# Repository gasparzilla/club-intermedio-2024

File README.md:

# Club Nivelacion Mustakis
Este es el repositorio del club de robótica de nivelación para el primer semestre. Aquí encontrás todo lo necesario para ejecutar las sesiones de manera exitosa.

## Sesiones
- Las presentaciones PPT por sesión se pueden encontrar en el siguiente link: [Presentaciones](https://drive.google.com/drive/folders/1Q9-XKyEnKL0MnVXYtlh8kp2lwUHTAggA?usp=drive_link).
- Los tiempos sugeridos por sesión se pueden encontrar en el siguiente link: [Tiempos](https://docs.google.com/spreadsheets/d/1nqdYl0ClQ_0Gk07j1FVFSghQwln12yA571QY8IFsEMs/edit?usp=sharing)
- Videos útiles complementarios a las sesiones se pueden encontrar en el siguiente link: [Videos](https://docs.google.com/document/d/1KKutP_OMOU2o7BTJ72E6Tdv1sluavG1waSLBUKC-ohQ/edit?usp=sharing)
- La lista de materiales por sesión se puede encontrar en el siguiente link: [Materiales](https://docs.google.com/spreadsheets/d/13yleChsTLTt9z9LAu8KrCemjK9vvLF0Dbb_VBI3P-Ws/edit?usp=sharing)

## Solucionarios
Los solucionarios se encuentran dentro de este repositorio ordenados por sesión.

## Archivos de construcción
En caso de ser necesario, dentro de la carpeta KiCad, se encuentran los proyectos originales de los circuitos utilizados en el semestre. Estos contienen los esquemáticos y el diseño de la pcb. También se pueden encontrar los archivos 3D necesarios.

## Errores y sugerencias
En caso de que se encuentren errores de contenido y/o cualquier otro problema relacionado a las sesiones, por favor añadirlo como una Issue al repositorio, de esta manera se queda registro de los cambios realizados historicamente para futuras referencias en un único lugar.

---
*Trabajo realizado por Benjamin Espinoza y Gaspas Fábrega para el programa de Ciencia y Tecnología de la Fundación Mustakis, 2024*

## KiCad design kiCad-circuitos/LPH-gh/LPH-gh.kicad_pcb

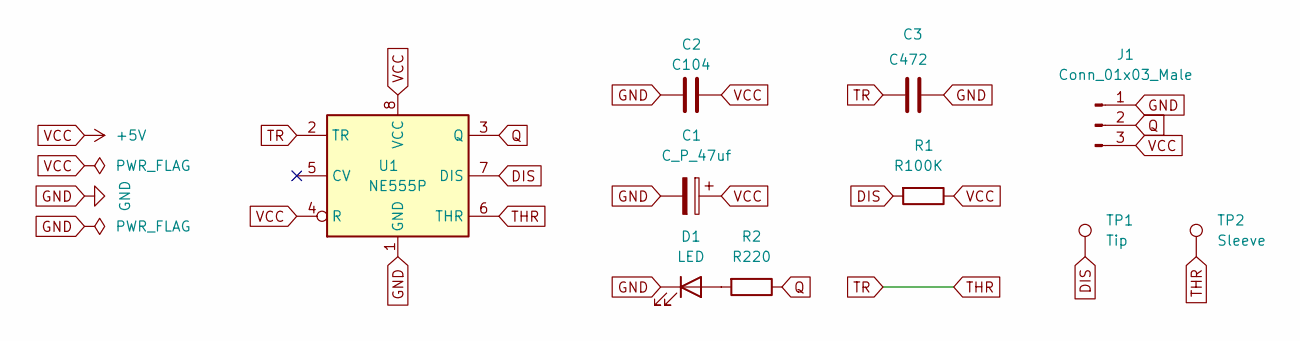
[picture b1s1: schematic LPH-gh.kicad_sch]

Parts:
C1: C_P_47uf; CP_Radial_D5.0mm_P2.00mm
C2: C104; C_Disc_D5.0mm_W2.5mm_P5.00mm
C3: C472; C_Disc_D5.0mm_W2.5mm_P5.00mm
D1: LED; LED_D5.0mm
J1: Conn_01x03_Male; PinHeader_1x03_P2.54mm_Vertical
R1: R100K; R_Axial_DIN0204_L3.6mm_D1.6mm_P7.62mm_Horizontal
R2: R220; R_Axial_DIN0204_L3.6mm_D1.6mm_P7.62mm_Horizontal
TP1: Tip; MountingHole_3mm_Pad
TP2: Sleeve; MountingHole_3mm_Pad
U1: NE555P; DIP-8_W7.62mm

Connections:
DIS: R1.2, TP1.1, U1.7 (DIS)
GND: C1.2, C2.2, C3.2, D1.1 (K), J1.1, U1.1 (GND)
unnamed: D1.2 (A), R2.2
Q: J1.2, R2.1, U1.3 (Q)
THR: C3.1, TP2.1, U1.2 (TR), U1.6 (THR)
VCC: C1.1, C2.1, J1.3, R1.1, U1.4 (R), U1.8 (VCC)

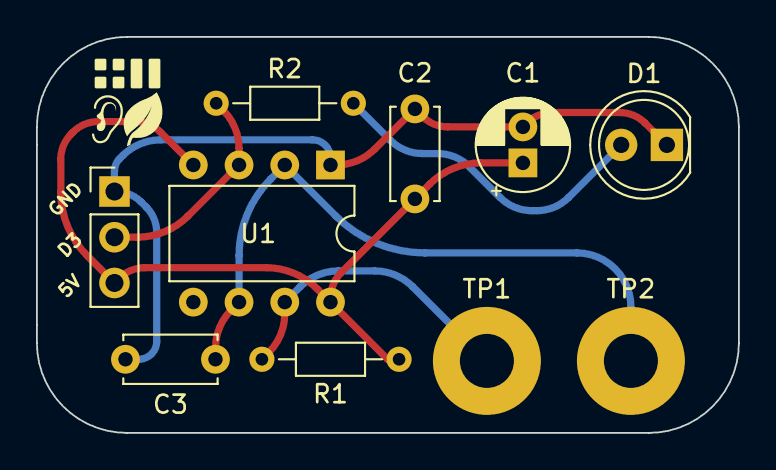
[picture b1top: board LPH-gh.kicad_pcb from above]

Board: 2 copper layers, 39.0 x 22.0 mm, 10 parts (0 on the bottom side), 6 nets.

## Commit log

2024-03-17 Solucionarios Sesion 2 y 4
2024-03-17 Solucionario sesion 3
2024-03-18 Solucion ejercicio alza del dolar
2024-03-18 Ejercicio intersección circunferencia
    Y además se arreglaron las rutas para que sean compatibles con arduino
2024-03-27 Pdfs
    Se añadieron los pdfs de la sesión 1 a la 5 y el libro completo
2024-03-28 Update README.md
    mi apellido no tiene s
2024-03-28 Fix pdfs
    Arreglos de circuitos
2024-03-28 Bases
    Bases para las sesiones 8-9-10 para rescue line y velocistas
2024-04-06 Videos complementarios
    Se añadió un link a un doc compartido para añadir links a videos útiles
2024-04-06 Actualización solucionario 2
    Se añadió un desafío a la parte del while con su respectiva solución
2024-04-06 Fix solucionario triangulos
    Se cambio una variable de in a float
2024-04-06 Arreglos de archivos
    Se arreglaron los nombres de los archivos para poder ejecutar arduino sin problema
2024-04-06 solucion indicador sin map
    Se añadio un nuevo archivo que corresponde a la solucion de la unidad 3
2024-04-07 Update EscuchaPlantas.ino
    eliminar configuraciones de pines que no se usan
2024-04-21 Materiales añadidos al readme
2024-04-23 test para el rene
2024-04-23 Funciones Serial Monitor
    2 funciones las cuales son para entrada y salida , lo cual mejora la interacción con el usuario - maquina , así lograr ejercicios de programación competitiva de manera mas intuitiva al programar .
2024-04-25 Update libro
    Se cambiaron todos los botones en los circuitos de 6x6 a 12x12
2024-04-30 Arreglo funciones input-output
    Se cambió de lugar las funciones creadas por el Rene, ya que tiene más sentido que esté en la sesión 4
2024-05-01 primera parte de los comentarios en espanol
2024-05-01 traduccion de comentarios completada
2024-05-07 modelos 3d cajas
2024-05-11 Update Ejercicio_triangulos.ino
    puse separados los inputs del desarrollo // muerte a la progra competitiva
2025-05-10 Actualizar Ejemplo_escritura_analoga.ino
